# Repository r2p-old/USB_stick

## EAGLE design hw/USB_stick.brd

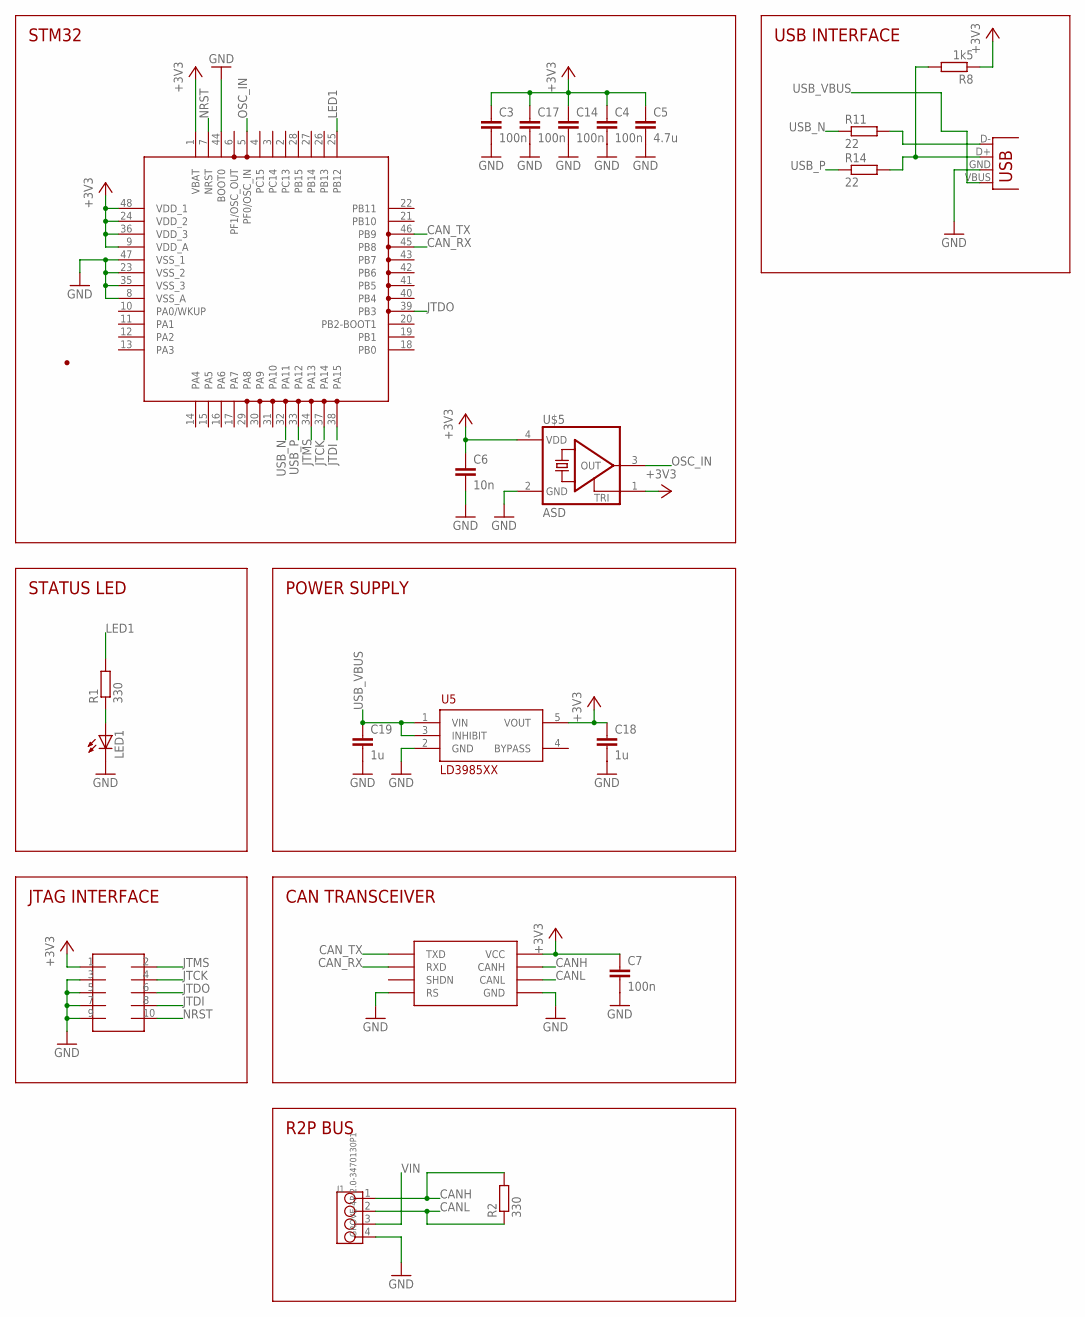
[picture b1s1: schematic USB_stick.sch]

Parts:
C3, C4, C7, C14, C17: 100n; C0603
C5: 4.7u; C0805
C6: 10n; C0603
C18, C19: 1u; C0603
J1: GROVE-4P-2.0-3470130P1; 4P-2.0
JP1: USB-A-H
LED1: LEDCHIPLED_0805; CHIPLED_0805
R1, R2: 330; R0603
R8: 1k5; R0603
R11, R14: 22; R0603
SOT1: MAX3051EKA; SOT23-8L
U5: LD3985XX; SOT23-5L
U$4: FTSH-105TH; FTSH-105-TH
U$5: ASD; 2.5X2
U$6: STM32F303C; LQFP48

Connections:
+3V3: C3.1, C4.1, C5.1, C6.1, C7.1, C14.1, C17.1, C18.1, R8.1, SOT1.3 (VCC), U5.5 (VOUT), U$4.1, U$5.1 (TRI), U$5.4 (VDD), U$6.1 (VBAT), U$6.9 (VDD_A), U$6.24 (VDD_2), U$6.36 (VDD_3), U$6.48 (VDD_1)
CANH: J1.1, R2.2, SOT1.7 (CANH)
CANL: J1.2, R2.1, SOT1.6 (CANL)
CAN_RX: SOT1.4 (RXD), U$6.45 (PB8)
CAN_TX: SOT1.1 (TXD), U$6.46 (PB9)
GND: C3.2, C4.2, C5.2, C6.2, C7.2, C14.2, C17.2, C18.2, C19.2, J1.4, JP1.GND (VBUS), LED1.C, SOT1.2 (GND), SOT1.8 (RS), U5.2 (GND), U$4.3, U$4.5, U$4.7, U$4.9, U$5.2 (GND), U$6.8 (VSS_A), U$6.23 (VSS_2), U$6.35 (VSS_3), U$6.44 (BOOT0), U$6.47 (VSS_1)
JTCK: U$4.4, U$6.37 (PA14)
JTDI: U$4.8, U$6.38 (PA15)
JTDO: U$4.6, U$6.39 (PB3)
JTMS: U$4.2, U$6.34 (PA13)
LED1: R1.2, U$6.25 (PB12)
unnamed: JP1.D- (D+), R11.2
unnamed: LED1.A, R1.1
unnamed: JP1.D+ (D-), R8.2, R14.2
NRST: U$4.10, U$6.7 (NRST)
OSC_IN: U$5.3 (OUT), U$6.5 (PF0/OSC_IN)
USB_N: R11.1, U$6.32 (PA11)
USB_P: R14.1, U$6.33 (PA12)
USB_VBUS: C19.1, JP1.VBUS (GND), U5.1 (VIN), U5.3 (INHIBIT)
VIN: J1.3

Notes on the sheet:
STM32
STATUS LED
JTAG INTERFACE
POWER SUPPLY
CAN TRANSCEIVER
R2P BUS
USB INTERFACE

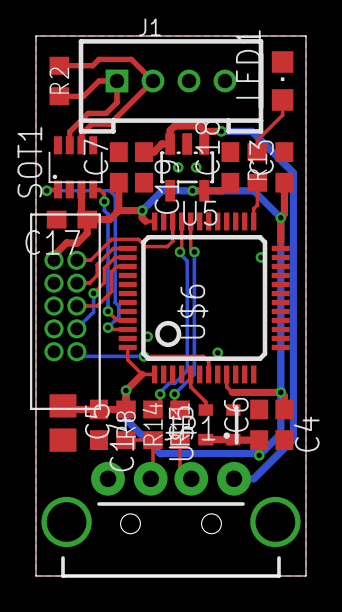
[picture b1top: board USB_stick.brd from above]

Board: 2 copper layers, 15.0 x 30.0 mm, 22 parts (0 on the bottom side), 19 nets.

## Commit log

2015-02-14 Layout complete
2015-02-19 Fixed directory creation
2015-02-19 Added bottom silkscreen

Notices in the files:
parts and their libraries:
SparkFun-Connectors: Licensing: CC v3.0 Share-Alike You are welcome to use this library for commercial purposes.
